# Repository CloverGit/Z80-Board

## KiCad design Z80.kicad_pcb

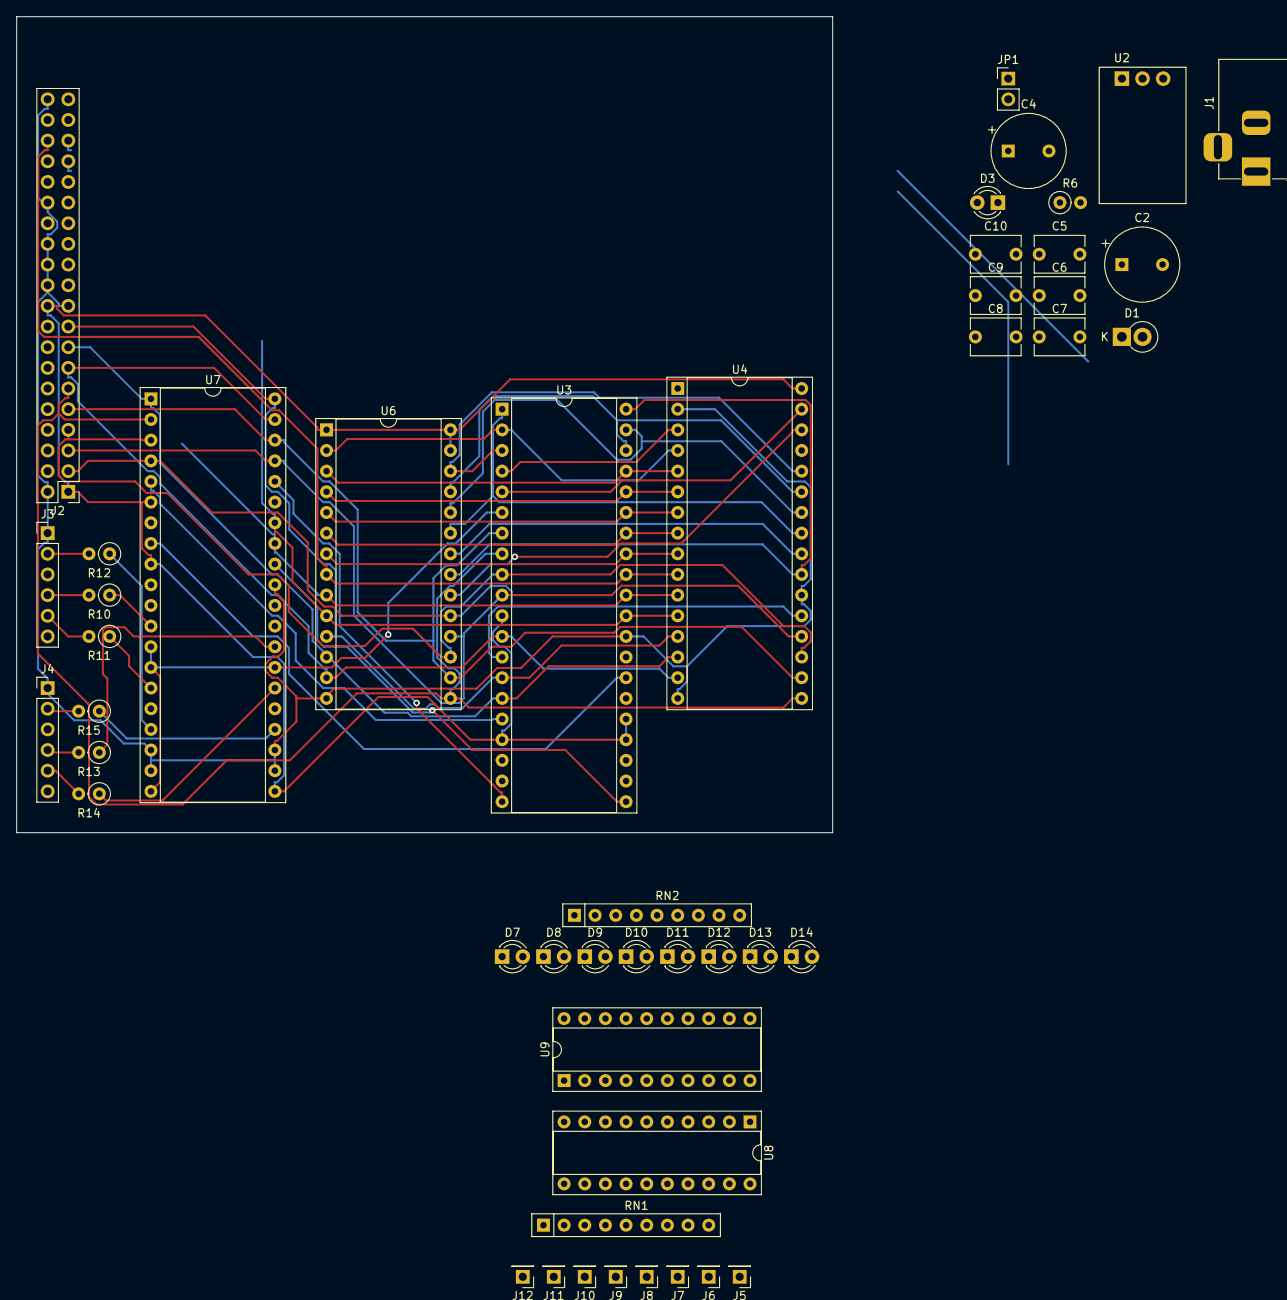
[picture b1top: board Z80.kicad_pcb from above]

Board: 2 copper layers, 100.3 x 100.3 mm, 47 parts (0 on the bottom side), 81 nets.

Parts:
C2: CP; CP_Radial_Tantal_D9.0mm_P5.00mm
C4: 0.1; CP_Radial_Tantal_D9.0mm_P5.00mm
C5, C6, C7, C8, C9, C10: 0.1; C_Disc_D6.0mm_W4.4mm_P5.00mm
D1: 1N540X; D_DO-15_P2.54mm_Vertical_KathodeUp
D3, D7, D8, D9, D10, D11, D12, D13, D14: LED; LED_D3.0mm
J1: Conn_Coaxial_Power; BarrelJack_Horizontal
J2: Conn_02x20_Odd_Even; PinHeader_2x20_P2.54mm_Vertical
J3, J4: Conn_01x06; PinHeader_1x06_P2.54mm_Vertical
J5: IN0; PinHeader_1x01_P2.54mm_Vertical
J6: IN1; PinHeader_1x01_P2.54mm_Vertical
J7: IN2; PinHeader_1x01_P2.54mm_Vertical
J8: IN3; PinHeader_1x01_P2.54mm_Vertical
J9: IN4; PinHeader_1x01_P2.54mm_Vertical
J10: IN5; PinHeader_1x01_P2.54mm_Vertical
J11: IN6; PinHeader_1x01_P2.54mm_Vertical
J12: IN7; PinHeader_1x01_P2.54mm_Vertical
JP1: Jumper; PinHeader_1x02_P2.54mm_Vertical
R6: 1K; R_Axial_DIN0207_L6.3mm_D2.5mm_P2.54mm_Vertical
R10, R11, R12, R13, R14, R15: 510R; R_Axial_DIN0207_L6.3mm_D2.5mm_P2.54mm_Vertical
RN1: 2K2; R_Array_SIP9
RN2: 390; R_Array_SIP9
U2: OKI-78SR-5_1.5-W36-C; Converter_DCDC_muRata_OKI-78SR_Horizontal
U3: Z80CPU; DIP-40_W15.24mm_Socket
U4: 628128; DIP-32_W15.24mm_Socket
U6: 27128; DIP-28_W15.24mm_Socket
U7: Z80_S100; DIP-40_W15.24mm_Socket
U8: 74LS245; DIP-20_W7.62mm_Socket
U9: 74LS374; DIP-20_W7.62mm_Socket

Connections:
/A0: J2.35, U3.30, U4.12, U6.10, U7.34
/A1: J2.33, U3.31, U4.11, U6.9, U7.33
/A2: J2.36, U3.32, U4.10, U6.8
/A3: U3.33, U4.9, U6.7
/A4: U3.34, U4.8, U6.6
/A5: U3.35, U4.7, U6.5
/A6: U3.36, U4.6, U6.4
/A7: U3.37, U4.5, U6.3
/A8: U3.38, U4.27, U6.25
/A9: U3.39, U4.26, U6.24
/A10: U3.40, U4.23, U6.21
/A11: U3.1, U4.25, U6.23
/A12: U3.2, U4.4, U6.2
/A13: U3.3, U4.28, U6.26
/A14: U3.4, U4.3
/A15: U3.5, U4.31
/D0: J2.17, U3.14, U4.13, U6.11, U7.40
/D1: J2.15, U3.15, U4.14, U6.12, U7.1
/D2: J2.13, U3.12, U4.15, U6.13, U7.39
/D3: J2.11, U3.8, U4.17, U6.15, U7.2
/D4: J2.9, U3.7, U4.18, U6.16, U7.38
/D5: J2.7, U3.9, U4.19, U6.17, U7.3
/D6: J2.5, U3.10, U4.20, U6.18, U7.37
/D7: J2.3, U3.13, U4.21, U6.19, U7.4
/MEMRD>: U4.24, U6.22
/RAMROM>: U4.30, U6.20
/ioport/D0: U8.2, U9.3
/ioport/D1: U8.3, U9.4
/ioport/D2: U8.4, U9.7
/ioport/D3: U8.5, U9.8
/ioport/D4: U8.6, U9.13
/ioport/D5: U8.7, U9.14
/ioport/D6: U8.8, U9.17
/ioport/D7: U8.9, U9.18
/~M1~: U3.27, U7.8
GND: C2.2, C4.2, C5.2, C6.2, C7.2, C8.2, C9.2, C10.2, J1.2, J2.2, J2.19, J2.22, J2.24, J2.26, J2.30, J2.40, J3.1, J4.1, R6.2, RN1.1, RN2.1, U2.2, U3.29, U4.2, U4.16, U4.22, U6.14, U7.18, U7.19, U7.22, U7.23, U7.31, U8.1, U8.10, U9.1, U9.10
unnamed: C2.1, D1.1, U2.1
unnamed: D1.2, J1.1
unnamed: D3.1, R6.1
unnamed: D7.1, RN2.2
unnamed: D7.2, U9.2
unnamed: D8.1, RN2.3
unnamed: D8.2, U9.5
unnamed: D9.1, RN2.4
unnamed: D9.2, U9.6
unnamed: D10.1, RN2.5
unnamed: D10.2, U9.9
unnamed: D11.1, RN2.6
unnamed: D11.2, U9.12
unnamed: D12.1, RN2.7
unnamed: D12.2, U9.15
unnamed: D13.1, RN2.8
unnamed: D13.2, U9.16
unnamed: D14.1, RN2.9
unnamed: D14.2, U9.19
unnamed: J3.2, R12.2
unnamed: J3.4, R10.2
unnamed: J3.5, R11.2
unnamed: J4.2, R15.2
unnamed: J4.4, R13.2
unnamed: J4.5, R14.2
unnamed: J5.~, RN1.9, U8.18
unnamed: J6.~, RN1.8, U8.17
unnamed: J7.~, RN1.7, U8.16
unnamed: J8.~, RN1.6, U8.15
unnamed: J9.~, RN1.5, U8.14
unnamed: J10.~, RN1.4, U8.13
unnamed: J11.~, RN1.3, U8.12
unnamed: J12.~, RN1.2, U8.11
unnamed: JP1.1, U2.3
unnamed: U3.16, U7.5
unnamed: R10.1, U7.12
unnamed: R11.1, U7.15
unnamed: R12.1, U7.17
unnamed: R13.1, U7.28
unnamed: R14.1, U7.26
unnamed: R15.1, U7.24
unnamed: U3.6, U7.13, U7.14, U7.20, U7.27
unnamed: U3.20, U7.36
unnamed: U3.21, U7.32
VCC: C4.1, C5.1, C6.1, C7.1, C8.1, C9.1, C10.1, D3.2, J2.1, J2.20, JP1.2, U3.11, U3.17, U3.24, U3.25, U4.32, U6.1, U6.27, U6.28, U7.6, U7.9, U7.21, U8.20, U9.20

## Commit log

2020-02-22 Update pcb and schematic
    pcb and schematic are drawn by CloverGit according to ioport.png and schematic.png
